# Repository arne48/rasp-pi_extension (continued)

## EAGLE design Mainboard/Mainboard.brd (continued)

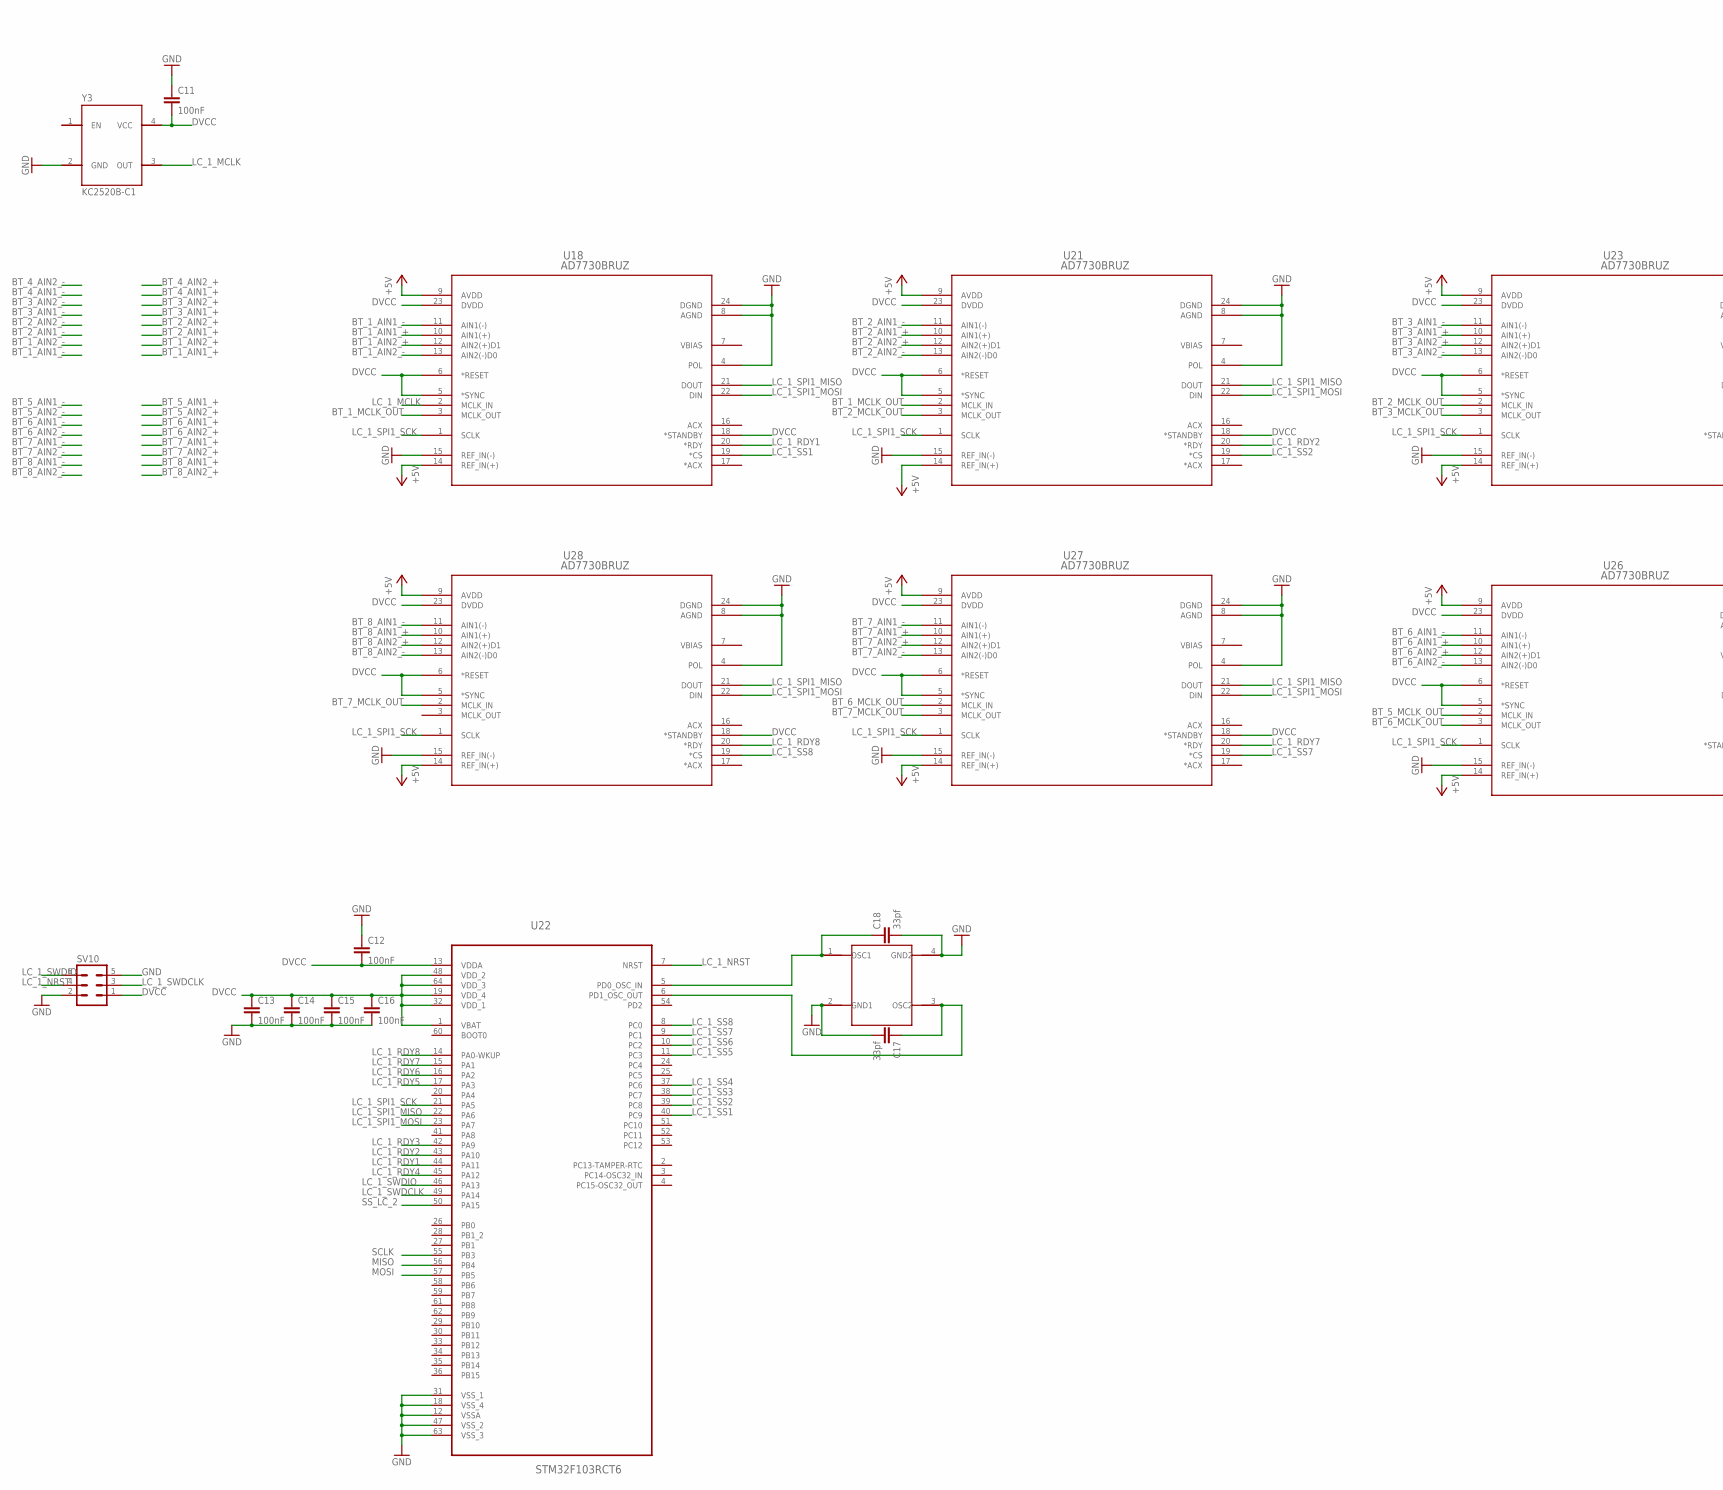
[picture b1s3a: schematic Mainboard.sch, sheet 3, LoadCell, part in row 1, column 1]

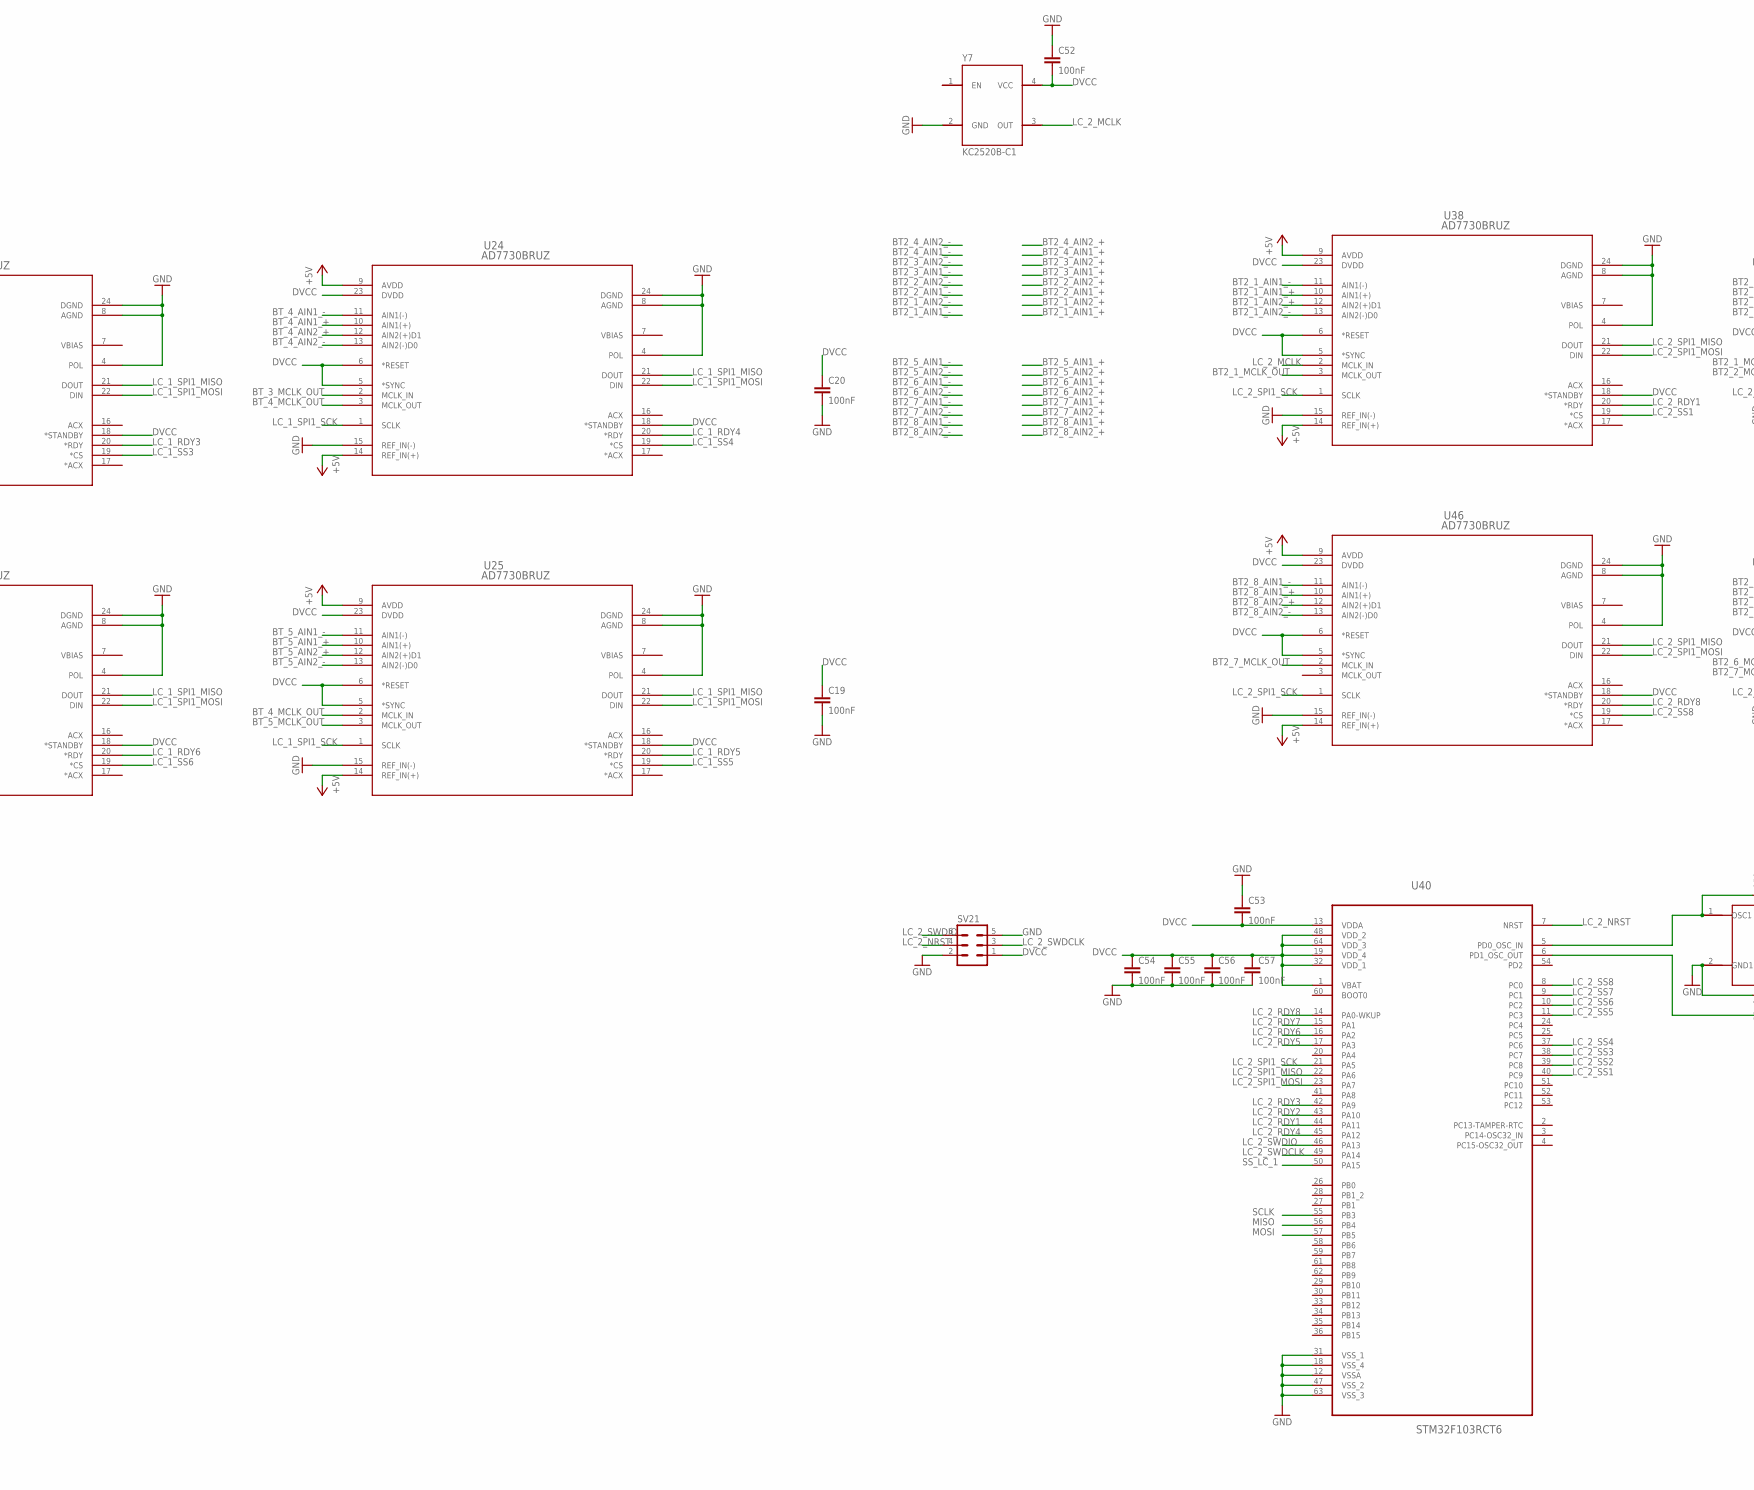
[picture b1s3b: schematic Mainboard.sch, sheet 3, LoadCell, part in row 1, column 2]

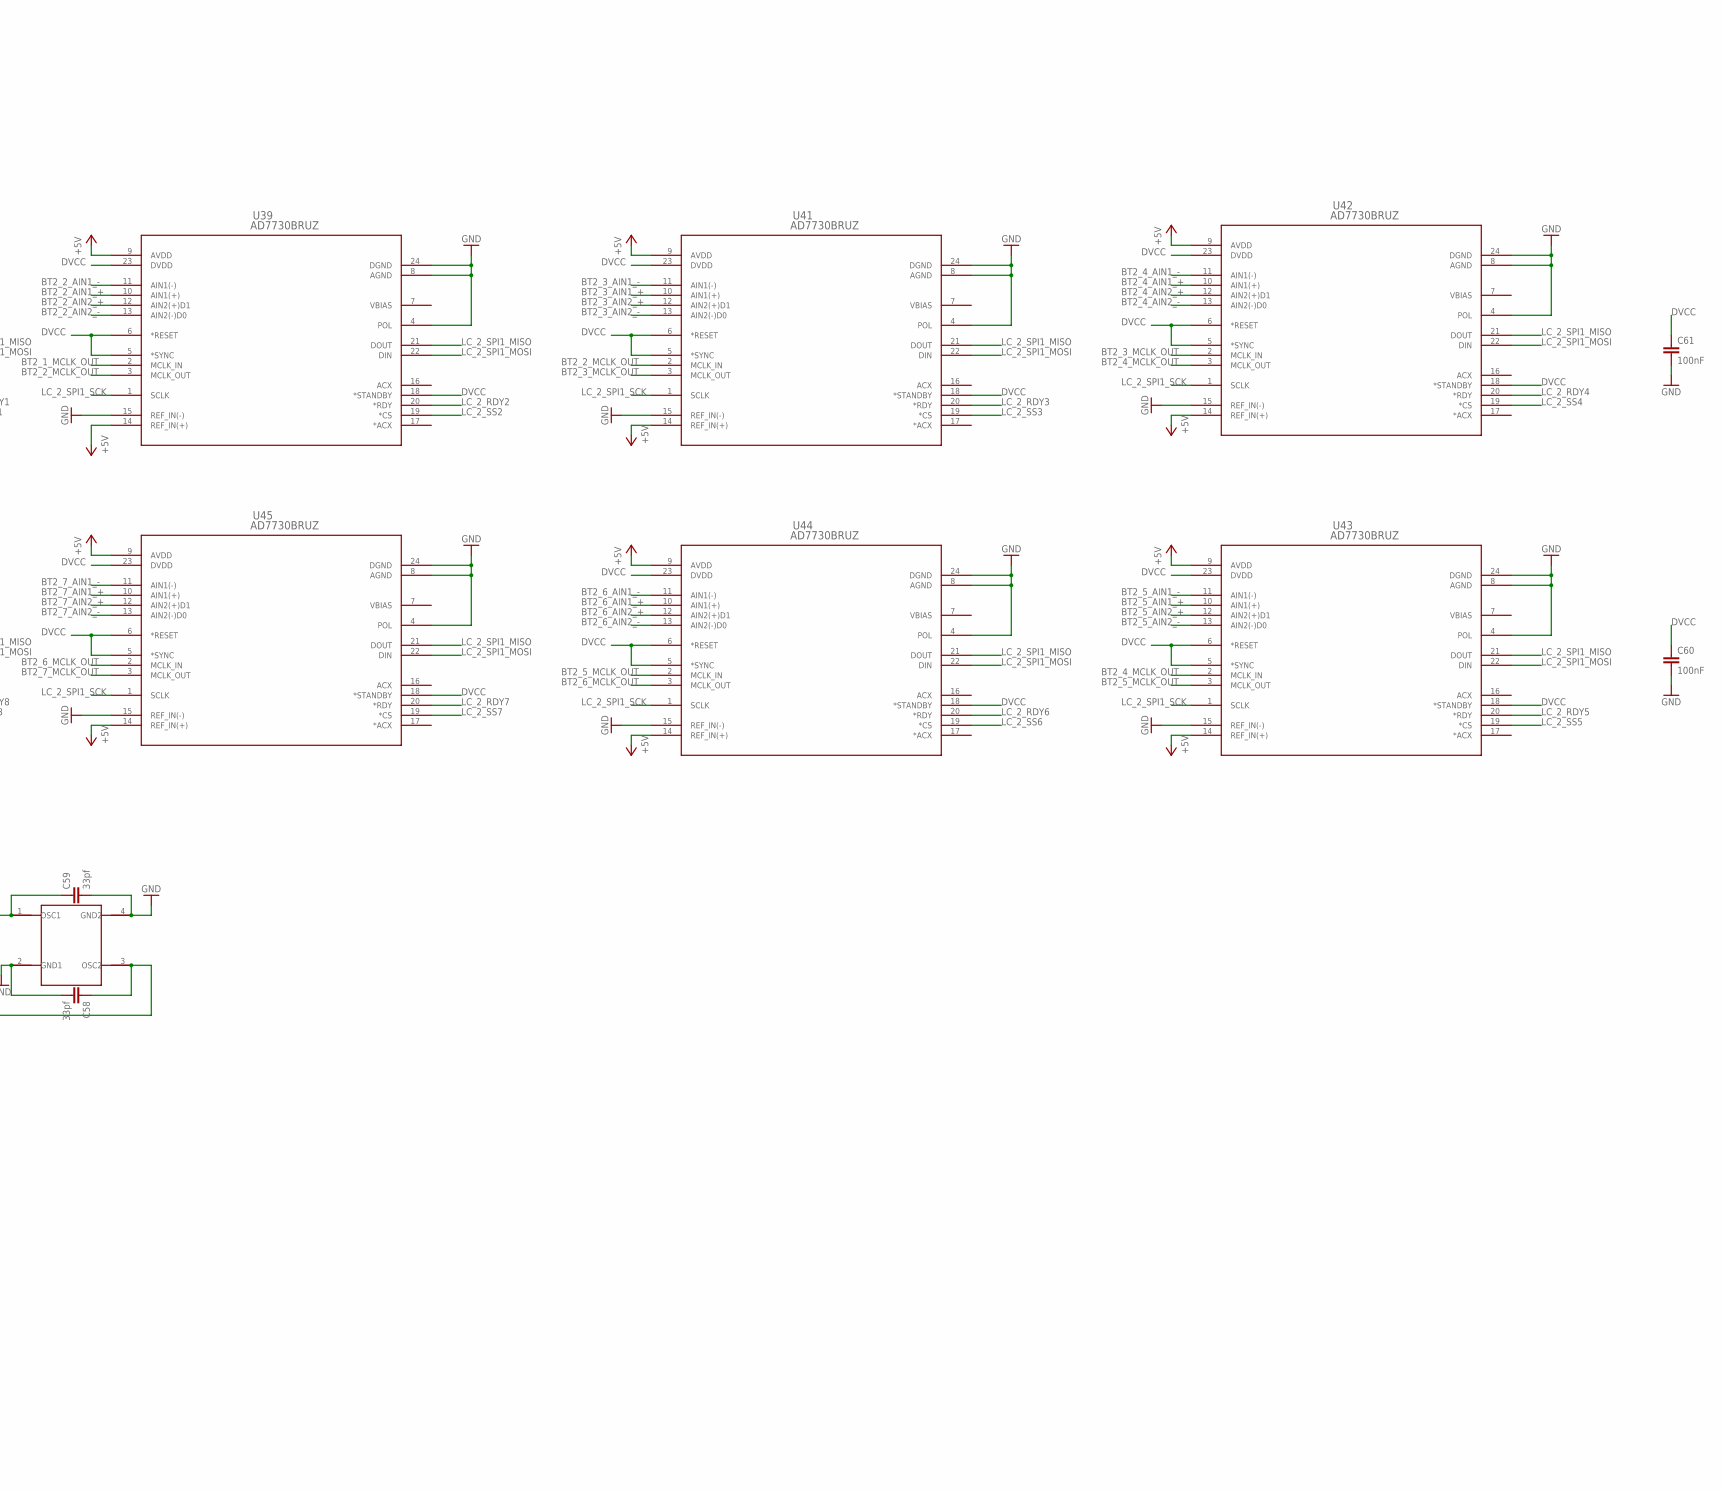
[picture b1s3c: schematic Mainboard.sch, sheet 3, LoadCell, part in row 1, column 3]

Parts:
C11, C12, C13, C14, C15, C16, C19, C20, C52, C53, C54, C55, C56, C57, C60, C61: 100nF; C0603
C17, C18, C58, C59: 33pf; C0603
SV10, SV21: MA03-2
U18, U21, U23, U24, U25, U26, U27, U28, U38, U39, U41, U42, U43, U44, U45, U46: AD7730BRUZ; RU_24
U22, U40: STM32F103RCT6; QFP50P1200X1200X160-64N
Y3, Y7: KC2520B-C1
Y4, Y8: ABM3B

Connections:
+5V: U18.9 (AVDD), U18.14 (REF_IN(+)), U21.9 (AVDD), U21.14 (REF_IN(+)), U23.9 (AVDD), U23.14 (REF_IN(+)), U24.9 (AVDD), U24.14 (REF_IN(+)), U25.9 (AVDD), U25.14 (REF_IN(+)), U26.9 (AVDD), U26.14 (REF_IN(+)), U27.9 (AVDD), U27.14 (REF_IN(+)), U28.9 (AVDD), U28.14 (REF_IN(+)), U38.9 (AVDD), U38.14 (REF_IN(+)), U39.9 (AVDD), U39.14 (REF_IN(+)), U41.9 (AVDD), U41.14 (REF_IN(+)), U42.9 (AVDD), U42.14 (REF_IN(+)), U43.9 (AVDD), U43.14 (REF_IN(+)), U44.9 (AVDD), U44.14 (REF_IN(+)), U45.9 (AVDD), U45.14 (REF_IN(+)), U46.9 (AVDD), U46.14 (REF_IN(+)); also elsewhere on the board
BT2_1_AIN1_+: U38.10 (AIN1(+)); also elsewhere on the board
BT2_1_AIN1_-: U38.11 (AIN1(-)); also elsewhere on the board
BT2_1_AIN2_+: U38.12 (AIN2(+)D1); also elsewhere on the board
BT2_1_AIN2_-: U38.13 (AIN2(-)D0); also elsewhere on the board
BT2_1_MCLK_OUT: U38.3 (MCLK_OUT), U39.2 (MCLK_IN)
BT2_2_AIN1_+: U39.10 (AIN1(+)); also elsewhere on the board
BT2_2_AIN1_-: U39.11 (AIN1(-)); also elsewhere on the board
BT2_2_AIN2_+: U39.12 (AIN2(+)D1); also elsewhere on the board
BT2_2_AIN2_-: U39.13 (AIN2(-)D0); also elsewhere on the board
BT2_2_MCLK_OUT: U39.3 (MCLK_OUT), U41.2 (MCLK_IN)
BT2_3_AIN1_+: U41.10 (AIN1(+)); also elsewhere on the board
BT2_3_AIN1_-: U41.11 (AIN1(-)); also elsewhere on the board
BT2_3_AIN2_+: U41.12 (AIN2(+)D1); also elsewhere on the board
BT2_3_AIN2_-: U41.13 (AIN2(-)D0); also elsewhere on the board
BT2_3_MCLK_OUT: U41.3 (MCLK_OUT), U42.2 (MCLK_IN)
BT2_4_AIN1_+: U42.10 (AIN1(+)); also elsewhere on the board
BT2_4_AIN1_-: U42.11 (AIN1(-)); also elsewhere on the board
BT2_4_AIN2_+: U42.12 (AIN2(+)D1); also elsewhere on the board
BT2_4_AIN2_-: U42.13 (AIN2(-)D0); also elsewhere on the board
BT2_4_MCLK_OUT: U42.3 (MCLK_OUT), U43.2 (MCLK_IN)
BT2_5_AIN1_+: U43.10 (AIN1(+)); also elsewhere on the board
BT2_5_AIN1_-: U43.11 (AIN1(-)); also elsewhere on the board
BT2_5_AIN2_+: U43.12 (AIN2(+)D1); also elsewhere on the board
BT2_5_AIN2_-: U43.13 (AIN2(-)D0); also elsewhere on the board
BT2_5_MCLK_OUT: U43.3 (MCLK_OUT), U44.2 (MCLK_IN)
BT2_6_AIN1_+: U44.10 (AIN1(+)); also elsewhere on the board
BT2_6_AIN1_-: U44.11 (AIN1(-)); also elsewhere on the board
BT2_6_AIN2_+: U44.12 (AIN2(+)D1); also elsewhere on the board
BT2_6_AIN2_-: U44.13 (AIN2(-)D0); also elsewhere on the board
BT2_6_MCLK_OUT: U44.3 (MCLK_OUT), U45.2 (MCLK_IN)
BT2_7_AIN1_+: U45.10 (AIN1(+)); also elsewhere on the board
BT2_7_AIN1_-: U45.11 (AIN1(-)); also elsewhere on the board
BT2_7_AIN2_+: U45.12 (AIN2(+)D1); also elsewhere on the board
BT2_7_AIN2_-: U45.13 (AIN2(-)D0); also elsewhere on the board
BT2_7_MCLK_OUT: U45.3 (MCLK_OUT), U46.2 (MCLK_IN)
BT2_8_AIN1_+: U46.10 (AIN1(+)); also elsewhere on the board
BT2_8_AIN1_-: U46.11 (AIN1(-)); also elsewhere on the board
BT2_8_AIN2_+: U46.12 (AIN2(+)D1); also elsewhere on the board
BT2_8_AIN2_-: U46.13 (AIN2(-)D0); also elsewhere on the board
BT_1_AIN1_+: U18.10 (AIN1(+)); also elsewhere on the board
BT_1_AIN1_-: U18.11 (AIN1(-)); also elsewhere on the board
BT_1_AIN2_+: U18.12 (AIN2(+)D1); also elsewhere on the board
BT_1_AIN2_-: U18.13 (AIN2(-)D0); also elsewhere on the board
BT_1_MCLK_OUT: U18.3 (MCLK_OUT), U21.2 (MCLK_IN)
BT_2_AIN1_+: U21.10 (AIN1(+)); also elsewhere on the board
BT_2_AIN1_-: U21.11 (AIN1(-)); also elsewhere on the board
BT_2_AIN2_+: U21.12 (AIN2(+)D1); also elsewhere on the board
BT_2_AIN2_-: U21.13 (AIN2(-)D0); also elsewhere on the board
BT_2_MCLK_OUT: U21.3 (MCLK_OUT), U23.2 (MCLK_IN)
BT_3_AIN1_+: U23.10 (AIN1(+)); also elsewhere on the board
BT_3_AIN1_-: U23.11 (AIN1(-)); also elsewhere on the board
BT_3_AIN2_+: U23.12 (AIN2(+)D1); also elsewhere on the board
BT_3_AIN2_-: U23.13 (AIN2(-)D0); also elsewhere on the board
BT_3_MCLK_OUT: U23.3 (MCLK_OUT), U24.2 (MCLK_IN)
BT_4_AIN1_+: U24.10 (AIN1(+)); also elsewhere on the board
BT_4_AIN1_-: U24.11 (AIN1(-)); also elsewhere on the board
BT_4_AIN2_+: U24.12 (AIN2(+)D1); also elsewhere on the board
BT_4_AIN2_-: U24.13 (AIN2(-)D0); also elsewhere on the board
BT_4_MCLK_OUT: U24.3 (MCLK_OUT), U25.2 (MCLK_IN)
BT_5_AIN1_+: U25.10 (AIN1(+)); also elsewhere on the board
BT_5_AIN1_-: U25.11 (AIN1(-)); also elsewhere on the board
BT_5_AIN2_+: U25.12 (AIN2(+)D1); also elsewhere on the board
BT_5_AIN2_-: U25.13 (AIN2(-)D0); also elsewhere on the board
BT_5_MCLK_OUT: U25.3 (MCLK_OUT), U26.2 (MCLK_IN)
BT_6_AIN1_+: U26.10 (AIN1(+)); also elsewhere on the board
BT_6_AIN1_-: U26.11 (AIN1(-)); also elsewhere on the board
BT_6_AIN2_+: U26.12 (AIN2(+)D1); also elsewhere on the board
BT_6_AIN2_-: U26.13 (AIN2(-)D0); also elsewhere on the board
BT_6_MCLK_OUT: U26.3 (MCLK_OUT), U27.2 (MCLK_IN)
BT_7_AIN1_+: U27.10 (AIN1(+)); also elsewhere on the board
BT_7_AIN1_-: U27.11 (AIN1(-)); also elsewhere on the board
BT_7_AIN2_+: U27.12 (AIN2(+)D1); also elsewhere on the board
BT_7_AIN2_-: U27.13 (AIN2(-)D0); also elsewhere on the board
BT_7_MCLK_OUT: U27.3 (MCLK_OUT), U28.2 (MCLK_IN)
BT_8_AIN1_+: U28.10 (AIN1(+)); also elsewhere on the board
BT_8_AIN1_-: U28.11 (AIN1(-)); also elsewhere on the board
BT_8_AIN2_+: U28.12 (AIN2(+)D1); also elsewhere on the board
BT_8_AIN2_-: U28.13 (AIN2(-)D0); also elsewhere on the board
DVCC: C11.2, C12.2, C13.1, C14.1, C15.1, C16.1, C19.1, C20.1, C52.2, C53.2, C54.1, C55.1, C56.1, C57.1, C60.1, C61.1, SV10.1, SV21.1, U18.5 (*SYNC), U18.6 (*RESET), U18.18 (*STANDBY), U18.23 (DVDD), U21.5 (*SYNC), U21.6 (*RESET), U21.18 (*STANDBY), U21.23 (DVDD), U22.1 (VBAT), U22.13 (VDDA), U22.19 (VDD_4), U22.32 (VDD_1), U22.48 (VDD_2), U22.64 (VDD_3), U23.5 (*SYNC), U23.6 (*RESET), U23.18 (*STANDBY), U23.23 (DVDD), U24.5 (*SYNC), U24.6 (*RESET), U24.18 (*STANDBY), U24.23 (DVDD), U25.5 (*SYNC), U25.6 (*RESET), U25.18 (*STANDBY), U25.23 (DVDD), U26.5 (*SYNC), U26.6 (*RESET), U26.18 (*STANDBY), U26.23 (DVDD), U27.5 (*SYNC), U27.6 (*RESET), U27.18 (*STANDBY), U27.23 (DVDD), U28.5 (*SYNC), U28.6 (*RESET), U28.18 (*STANDBY), U28.23 (DVDD), U38.5 (*SYNC), U38.6 (*RESET), U38.18 (*STANDBY), U38.23 (DVDD), U39.5 (*SYNC), U39.6 (*RESET), U39.18 (*STANDBY), U39.23 (DVDD), U40.1 (VBAT), U40.13 (VDDA), U40.19 (VDD_4), U40.32 (VDD_1), U40.48 (VDD_2), U40.64 (VDD_3), U41.5 (*SYNC), U41.6 (*RESET), U41.18 (*STANDBY), U41.23 (DVDD), U42.5 (*SYNC), U42.6 (*RESET), U42.18 (*STANDBY), U42.23 (DVDD), U43.5 (*SYNC), U43.6 (*RESET), U43.18 (*STANDBY), U43.23 (DVDD), U44.5 (*SYNC), U44.6 (*RESET), U44.18 (*STANDBY), U44.23 (DVDD), U45.5 (*SYNC), U45.6 (*RESET), U45.18 (*STANDBY), U45.23 (DVDD), U46.5 (*SYNC), U46.6 (*RESET), U46.18 (*STANDBY), U46.23 (DVDD), Y3.4 (VCC), Y7.4 (VCC); also elsewhere on the board
GND: C11.1, C12.1, C13.2, C14.2, C15.2, C16.2, C17.2, C18.2, C19.2, C20.2, C52.1, C53.1, C54.2, C55.2, C56.2, C57.2, C58.2, C59.2, C60.2, C61.2, SV10.2, SV10.5, SV21.2, SV21.5, U18.4 (POL), U18.8 (AGND), U18.15 (REF_IN(-)), U18.24 (DGND), U21.4 (POL), U21.8 (AGND), U21.15 (REF_IN(-)), U21.24 (DGND), U22.12 (VSSA), U22.18 (VSS_4), U22.31 (VSS_1), U22.47 (VSS_2), U22.63 (VSS_3), U23.4 (POL), U23.8 (AGND), U23.15 (REF_IN(-)), U23.24 (DGND), U24.4 (POL), U24.8 (AGND), U24.15 (REF_IN(-)), U24.24 (DGND), U25.4 (POL), U25.8 (AGND), U25.15 (REF_IN(-)), U25.24 (DGND), U26.4 (POL), U26.8 (AGND), U26.15 (REF_IN(-)), U26.24 (DGND), U27.4 (POL), U27.8 (AGND), U27.15 (REF_IN(-)), U27.24 (DGND), U28.4 (POL), U28.8 (AGND), U28.15 (REF_IN(-)), U28.24 (DGND), U38.4 (POL), U38.8 (AGND), U38.15 (REF_IN(-)), U38.24 (DGND), U39.4 (POL), U39.8 (AGND), U39.15 (REF_IN(-)), U39.24 (DGND), U40.12 (VSSA), U40.18 (VSS_4), U40.31 (VSS_1), U40.47 (VSS_2), U40.63 (VSS_3), U41.4 (POL), U41.8 (AGND), U41.15 (REF_IN(-)), U41.24 (DGND), U42.4 (POL), U42.8 (AGND), U42.15 (REF_IN(-)), U42.24 (DGND), U43.4 (POL), U43.8 (AGND), U43.15 (REF_IN(-)), U43.24 (DGND), U44.4 (POL), U44.8 (AGND), U44.15 (REF_IN(-)), U44.24 (DGND), U45.4 (POL), U45.8 (AGND), U45.15 (REF_IN(-)), U45.24 (DGND), U46.4 (POL), U46.8 (AGND), U46.15 (REF_IN(-)), U46.24 (DGND), Y3.2 (GND), Y4.2 (GND1), Y4.4 (GND2), Y7.2 (GND), Y8.2 (GND1), Y8.4 (GND2); also elsewhere on the board
LC_1_MCLK: U18.2 (MCLK_IN), Y3.3 (OUT)
LC_1_NRST: SV10.4, U22.7 (NRST)
LC_1_RDY1: U18.20 (*RDY), U22.44 (PA11)
LC_1_RDY2: U21.20 (*RDY), U22.43 (PA10)
LC_1_RDY3: U22.42 (PA9), U23.20 (*RDY)
LC_1_RDY4: U22.45 (PA12), U24.20 (*RDY)
LC_1_RDY5: U22.17 (PA3), U25.20 (*RDY)
LC_1_RDY6: U22.16 (PA2), U26.20 (*RDY)
LC_1_RDY7: U22.15 (PA1), U27.20 (*RDY)
LC_1_RDY8: U22.14 (PA0-WKUP), U28.20 (*RDY)
LC_1_SPI1_MISO: U18.21 (DOUT), U21.21 (DOUT), U22.22 (PA6), U23.21 (DOUT), U24.21 (DOUT), U25.21 (DOUT), U26.21 (DOUT), U27.21 (DOUT), U28.21 (DOUT)
LC_1_SPI1_MOSI: U18.22 (DIN), U21.22 (DIN), U22.23 (PA7), U23.22 (DIN), U24.22 (DIN), U25.22 (DIN), U26.22 (DIN), U27.22 (DIN), U28.22 (DIN)
LC_1_SPI1_SCK: U18.1 (SCLK), U21.1 (SCLK), U22.21 (PA5), U23.1 (SCLK), U24.1 (SCLK), U25.1 (SCLK), U26.1 (SCLK), U27.1 (SCLK), U28.1 (SCLK)
LC_1_SS1: U18.19 (*CS), U22.40 (PC9)
LC_1_SS2: U21.19 (*CS), U22.39 (PC8)
LC_1_SS3: U22.38 (PC7), U23.19 (*CS)
LC_1_SS4: U22.37 (PC6), U24.19 (*CS)
LC_1_SS5: U22.11 (PC3), U25.19 (*CS)
LC_1_SS6: U22.10 (PC2), U26.19 (*CS)
LC_1_SS7: U22.9 (PC1), U27.19 (*CS)
LC_1_SS8: U22.8 (PC0), U28.19 (*CS)
LC_1_SWDCLK: SV10.3, U22.49 (PA14)
LC_1_SWDIO: SV10.6, U22.46 (PA13)
LC_2_MCLK: U38.2 (MCLK_IN), Y7.3 (OUT)
LC_2_NRST: SV21.4, U40.7 (NRST)
LC_2_RDY1: U38.20 (*RDY), U40.44 (PA11)
LC_2_RDY2: U39.20 (*RDY), U40.43 (PA10)
LC_2_RDY3: U40.42 (PA9), U41.20 (*RDY)
LC_2_RDY4: U40.45 (PA12), U42.20 (*RDY)
LC_2_RDY5: U40.17 (PA3), U43.20 (*RDY)
LC_2_RDY6: U40.16 (PA2), U44.20 (*RDY)
LC_2_RDY7: U40.15 (PA1), U45.20 (*RDY)
LC_2_RDY8: U40.14 (PA0-WKUP), U46.20 (*RDY)
LC_2_SPI1_MISO: U38.21 (DOUT), U39.21 (DOUT), U40.22 (PA6), U41.21 (DOUT), U42.21 (DOUT), U43.21 (DOUT), U44.21 (DOUT), U45.21 (DOUT), U46.21 (DOUT)
LC_2_SPI1_MOSI: U38.22 (DIN), U39.22 (DIN), U40.23 (PA7), U41.22 (DIN), U42.22 (DIN), U43.22 (DIN), U44.22 (DIN), U45.22 (DIN), U46.22 (DIN)
LC_2_SPI1_SCK: U38.1 (SCLK), U39.1 (SCLK), U40.21 (PA5), U41.1 (SCLK), U42.1 (SCLK), U43.1 (SCLK), U44.1 (SCLK), U45.1 (SCLK), U46.1 (SCLK)
LC_2_SS1: U38.19 (*CS), U40.40 (PC9)
LC_2_SS2: U39.19 (*CS), U40.39 (PC8)
LC_2_SS3: U40.38 (PC7), U41.19 (*CS)
LC_2_SS4: U40.37 (PC6), U42.19 (*CS)
LC_2_SS5: U40.11 (PC3), U43.19 (*CS)
LC_2_SS6: U40.10 (PC2), U44.19 (*CS)
LC_2_SS7: U40.9 (PC1), U45.19 (*CS)
LC_2_SS8: U40.8 (PC0), U46.19 (*CS)
LC_2_SWDCLK: SV21.3, U40.49 (PA14)
LC_2_SWDIO: SV21.6, U40.46 (PA13)
MISO: U22.56 (PB4), U40.56 (PB4); also elsewhere on the board
MOSI: U22.57 (PB5), U40.57 (PB5); also elsewhere on the board
unnamed: C18.1, U22.5 (PD0_OSC_IN), Y4.1 (OSC1)
unnamed: C17.1, U22.6 (PD1_OSC_OUT), Y4.3 (OSC2)
unnamed: C59.1, U40.5 (PD0_OSC_IN), Y8.1 (OSC1)
unnamed: C58.1, U40.6 (PD1_OSC_OUT), Y8.3 (OSC2)
PB7: U22.59 (PB7), U40.59 (PB7)
SCLK: U22.55 (PB3), U40.55 (PB3); also elsewhere on the board
SS_LC_1: U40.50 (PA15); also elsewhere on the board
SS_LC_2: U22.50 (PA15); also elsewhere on the board

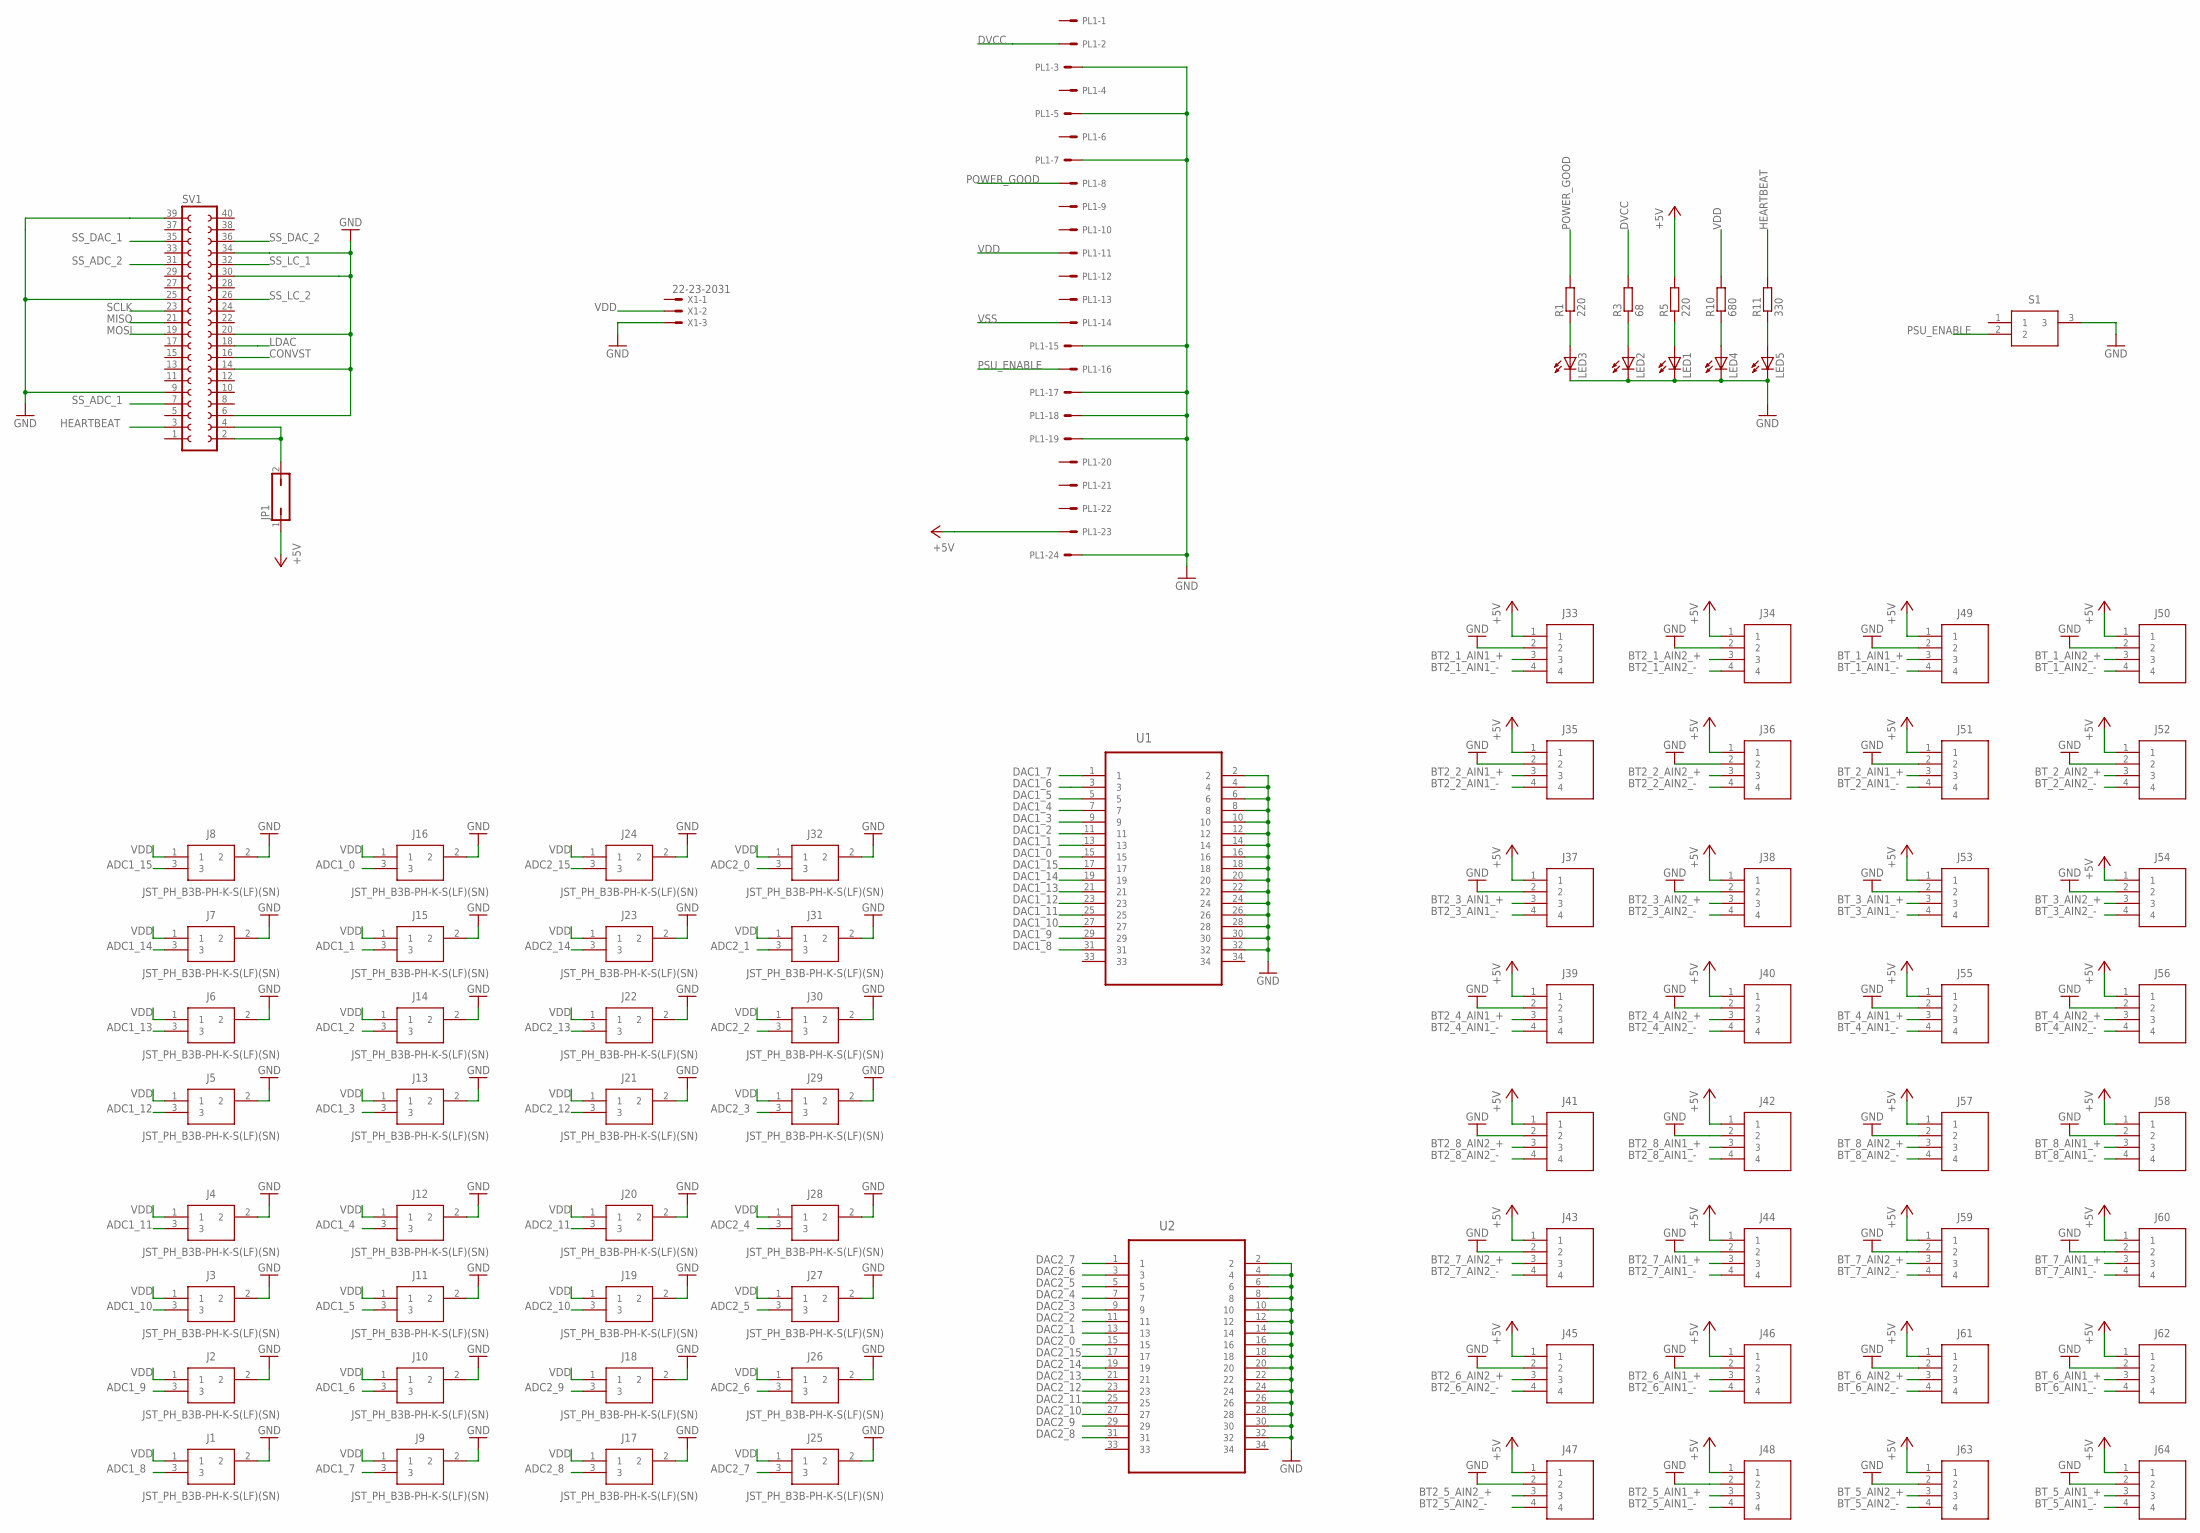
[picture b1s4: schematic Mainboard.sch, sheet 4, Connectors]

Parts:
J1, J2, J3, J4, J5, J6, J7, J8, J9, J10, J11, J12, J13, J14, J15, J16, J17, J18, J19, J20, J21, J22, J23, J24, J25, J26, J27, J28, J29, J30, J31, J32: JST_PH_B3B-PH-K-S(LF)(SN); JST_PH_SHDR3W50P0X200_1X3_790X450X600
J33, J34, J35, J36, J37, J38, J39, J40, J41, J42, J43, J44, J45, J46, J47, J48, J49, J50, J51, J52, J53, J54, J55, J56, J57, J58, J59, J60, J61, J62, J63, J64: B4B-PH-K-S(LF)(SN); SHDR4W50P0X200_1X4_990X450X600
JP1: JP1Q; JP1
LED1, LED2, LED3, LED4, LED5: TLLG4400; LED3MM
PL1: 555X-24V; 5566-24
R1, R5: 220; R0805
R3: 68; R0805
R10: 680; R0805
R11: 330; R0805
S1: 1MS1T1B1M2QES-5
SV1: FE20-2
U1, U2: AMP-5103309-7-34PIN_5103309-7; AMP-5103309-7-34PIN_TYCO_5103309-7
X1: 22-23-2031

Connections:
+5V: J33.1, J34.1, J35.1, J36.1, J37.1, J38.1, J39.1, J40.1, J41.1, J42.1, J43.1, J44.1, J45.1, J46.1, J47.1, J48.1, J49.1, J50.1, J51.1, J52.1, J53.1, J54.1, J55.1, J56.1, J57.1, J58.1, J59.1, J60.1, J61.1, J62.1, J63.1, J64.1, JP1.1, PL1.23, R5.2; also elsewhere on the board
ADC1_0: J16.3; also elsewhere on the board
ADC1_1: J15.3; also elsewhere on the board
ADC1_2: J14.3; also elsewhere on the board
ADC1_3: J13.3; also elsewhere on the board
ADC1_4: J12.3; also elsewhere on the board
ADC1_5: J11.3; also elsewhere on the board
ADC1_6: J10.3; also elsewhere on the board
ADC1_7: J9.3; also elsewhere on the board
ADC1_8: J1.3; also elsewhere on the board
ADC1_9: J2.3; also elsewhere on the board
ADC1_10: J3.3; also elsewhere on the board
ADC1_11: J4.3; also elsewhere on the board
ADC1_12: J5.3; also elsewhere on the board
ADC1_13: J6.3; also elsewhere on the board
ADC1_14: J7.3; also elsewhere on the board
ADC1_15: J8.3; also elsewhere on the board
ADC2_0: J32.3; also elsewhere on the board
ADC2_1: J31.3; also elsewhere on the board
ADC2_2: J30.3; also elsewhere on the board
ADC2_3: J29.3; also elsewhere on the board
ADC2_4: J28.3; also elsewhere on the board
ADC2_5: J27.3; also elsewhere on the board
ADC2_6: J26.3; also elsewhere on the board
ADC2_7: J25.3; also elsewhere on the board
ADC2_8: J17.3; also elsewhere on the board
ADC2_9: J18.3; also elsewhere on the board
ADC2_10: J19.3; also elsewhere on the board
ADC2_11: J20.3; also elsewhere on the board
ADC2_12: J21.3; also elsewhere on the board
ADC2_13: J22.3; also elsewhere on the board
ADC2_14: J23.3; also elsewhere on the board
ADC2_15: J24.3; also elsewhere on the board
BT2_1_AIN1_+: J33.3; also elsewhere on the board
BT2_1_AIN1_-: J33.4; also elsewhere on the board
BT2_1_AIN2_+: J34.3; also elsewhere on the board
BT2_1_AIN2_-: J34.4; also elsewhere on the board
BT2_2_AIN1_+: J35.3; also elsewhere on the board
BT2_2_AIN1_-: J35.4; also elsewhere on the board
BT2_2_AIN2_+: J36.3; also elsewhere on the board
BT2_2_AIN2_-: J36.4; also elsewhere on the board
BT2_3_AIN1_+: J37.3; also elsewhere on the board
BT2_3_AIN1_-: J37.4; also elsewhere on the board
BT2_3_AIN2_+: J38.3; also elsewhere on the board
BT2_3_AIN2_-: J38.4; also elsewhere on the board
BT2_4_AIN1_+: J39.3; also elsewhere on the board
BT2_4_AIN1_-: J39.4; also elsewhere on the board
BT2_4_AIN2_+: J40.3; also elsewhere on the board
BT2_4_AIN2_-: J40.4; also elsewhere on the board
BT2_5_AIN1_+: J48.3; also elsewhere on the board
BT2_5_AIN1_-: J48.4; also elsewhere on the board
BT2_5_AIN2_+: J47.3; also elsewhere on the board
BT2_5_AIN2_-: J47.4; also elsewhere on the board
BT2_6_AIN1_+: J46.3; also elsewhere on the board
BT2_6_AIN1_-: J46.4; also elsewhere on the board
BT2_6_AIN2_+: J45.3; also elsewhere on the board
BT2_6_AIN2_-: J45.4; also elsewhere on the board
BT2_7_AIN1_+: J44.3; also elsewhere on the board
BT2_7_AIN1_-: J44.4; also elsewhere on the board
BT2_7_AIN2_+: J43.3; also elsewhere on the board
BT2_7_AIN2_-: J43.4; also elsewhere on the board
BT2_8_AIN1_+: J42.3; also elsewhere on the board
BT2_8_AIN1_-: J42.4; also elsewhere on the board
BT2_8_AIN2_+: J41.3; also elsewhere on the board
BT2_8_AIN2_-: J41.4; also elsewhere on the board
BT_1_AIN1_+: J49.3; also elsewhere on the board
BT_1_AIN1_-: J49.4; also elsewhere on the board
BT_1_AIN2_+: J50.3; also elsewhere on the board
BT_1_AIN2_-: J50.4; also elsewhere on the board
BT_2_AIN1_+: J51.3; also elsewhere on the board
BT_2_AIN1_-: J51.4; also elsewhere on the board
BT_2_AIN2_+: J52.3; also elsewhere on the board
BT_2_AIN2_-: J52.4; also elsewhere on the board
BT_3_AIN1_+: J53.3; also elsewhere on the board
BT_3_AIN1_-: J53.4; also elsewhere on the board
BT_3_AIN2_+: J54.3; also elsewhere on the board
BT_3_AIN2_-: J54.4; also elsewhere on the board
BT_4_AIN1_+: J55.3; also elsewhere on the board
BT_4_AIN1_-: J55.4; also elsewhere on the board
BT_4_AIN2_+: J56.3; also elsewhere on the board
BT_4_AIN2_-: J56.4; also elsewhere on the board
BT_5_AIN1_+: J64.3; also elsewhere on the board
BT_5_AIN1_-: J64.4; also elsewhere on the board
BT_5_AIN2_+: J63.3; also elsewhere on the board
BT_5_AIN2_-: J63.4; also elsewhere on the board
BT_6_AIN1_+: J62.3; also elsewhere on the board
BT_6_AIN1_-: J62.4; also elsewhere on the board
BT_6_AIN2_+: J61.3; also elsewhere on the board
BT_6_AIN2_-: J61.4; also elsewhere on the board
BT_7_AIN1_+: J60.3; also elsewhere on the board
BT_7_AIN1_-: J60.4; also elsewhere on the board
BT_7_AIN2_+: J59.3; also elsewhere on the board
BT_7_AIN2_-: J59.4; also elsewhere on the board
BT_8_AIN1_+: J58.3; also elsewhere on the board
BT_8_AIN1_-: J58.4; also elsewhere on the board
BT_8_AIN2_+: J57.3; also elsewhere on the board
BT_8_AIN2_-: J57.4; also elsewhere on the board
CONVST: SV1.16; also elsewhere on the board
DAC1_0: U1.15; also elsewhere on the board
DAC1_1: U1.13; also elsewhere on the board
DAC1_2: U1.11; also elsewhere on the board
DAC1_3: U1.9; also elsewhere on the board
DAC1_4: U1.7; also elsewhere on the board
DAC1_5: U1.5; also elsewhere on the board
DAC1_6: U1.3; also elsewhere on the board
DAC1_7: U1.1; also elsewhere on the board
DAC1_8: U1.31; also elsewhere on the board
DAC1_9: U1.29; also elsewhere on the board
DAC1_10: U1.27; also elsewhere on the board
DAC1_11: U1.25; also elsewhere on the board
DAC1_12: U1.23; also elsewhere on the board
DAC1_13: U1.21; also elsewhere on the board
DAC1_14: U1.19; also elsewhere on the board
DAC1_15: U1.17; also elsewhere on the board
DAC2_0: U2.15; also elsewhere on the board
DAC2_1: U2.13; also elsewhere on the board
DAC2_2: U2.11; also elsewhere on the board
DAC2_3: U2.9; also elsewhere on the board
DAC2_4: U2.7; also elsewhere on the board
DAC2_5: U2.5; also elsewhere on the board
DAC2_6: U2.3; also elsewhere on the board
DAC2_7: U2.1; also elsewhere on the board
DAC2_8: U2.31; also elsewhere on the board
DAC2_9: U2.29; also elsewhere on the board
DAC2_10: U2.27; also elsewhere on the board
DAC2_11: U2.25; also elsewhere on the board
DAC2_12: U2.23; also elsewhere on the board
DAC2_13: U2.21; also elsewhere on the board
DAC2_14: U2.19; also elsewhere on the board
DAC2_15: U2.17; also elsewhere on the board
DVCC: PL1.2, R3.2; also elsewhere on the board
GND: J1.2, J2.2, J3.2, J4.2, J5.2, J6.2, J7.2, J8.2, J9.2, J10.2, J11.2, J12.2, J13.2, J14.2, J15.2, J16.2, J17.2, J18.2, J19.2, J20.2, J21.2, J22.2, J23.2, J24.2, J25.2, J26.2, J27.2, J28.2, J29.2, J30.2, J31.2, J32.2, J33.2, J34.2, J35.2, J36.2, J37.2, J38.2, J39.2, J40.2, J41.2, J42.2, J43.2, J44.2, J45.2, J46.2, J47.2, J48.2, J49.2, J50.2, J51.2, J52.2, J53.2, J54.2, J55.2, J56.2, J57.2, J58.2, J59.2, J60.2, J61.2, J62.2, J63.2, J64.2, LED1.K (C), LED2.K (C), LED3.K (C), LED4.K (C), LED5.K (C), PL1.3, PL1.5, PL1.7, PL1.15, PL1.17, PL1.18, PL1.19, PL1.24, S1.3, SV1.6, SV1.9, SV1.14, SV1.20, SV1.25, SV1.30, SV1.34, SV1.39, U1.2, U1.4, U1.6, U1.8, U1.10, U1.12, U1.14, U1.16, U1.18, U1.20, U1.22, U1.24, U1.26, U1.28, U1.30, U1.32, U2.2, U2.4, U2.6, U2.8, U2.10, U2.12, U2.14, U2.16, U2.18, U2.20, U2.22, U2.24, U2.26, U2.28, U2.30, U2.32, X1.3; also elsewhere on the board
HEARTBEAT: R11.2, SV1.3
LDAC: SV1.18; also elsewhere on the board
MISO: SV1.21; also elsewhere on the board
MOSI: SV1.19; also elsewhere on the board
unnamed: JP1.2, SV1.2, SV1.4
unnamed: LED3.A, R1.1
unnamed: LED2.A, R3.1
unnamed: LED1.A, R5.1
unnamed: LED4.A, R10.1
unnamed: LED5.A, R11.1
POWER_GOOD: PL1.8, R1.2
PSU_ENABLE: PL1.16, S1.2
SCLK: SV1.23; also elsewhere on the board
SS_ADC_1: SV1.7; also elsewhere on the board
SS_ADC_2: SV1.31; also elsewhere on the board
SS_DAC_1: SV1.35; also elsewhere on the board
SS_DAC_2: SV1.36; also elsewhere on the board
SS_LC_1: SV1.32; also elsewhere on the board
SS_LC_2: SV1.26; also elsewhere on the board
VDD: J1.1, J2.1, J3.1, J4.1, J5.1, J6.1, J7.1, J8.1, J9.1, J10.1, J11.1, J12.1, J13.1, J14.1, J15.1, J16.1, J17.1, J18.1, J19.1, J20.1, J21.1, J22.1, J23.1, J24.1, J25.1, J26.1, J27.1, J28.1, J29.1, J30.1, J31.1, J32.1, PL1.11, R10.2, X1.2; also elsewhere on the board
VSS: PL1.14; also elsewhere on the board

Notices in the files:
parts and their libraries:
SparkFun-Switches: Licensing: Creative Commons ShareAlike 4.0 International - https://creativecommons.org/licenses/by-sa/4.0
